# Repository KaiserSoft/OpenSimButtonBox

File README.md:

Modular Open Sim Racing Button Box
==================================

The Modular Open Button Box (MOBB) project is a complete open source solution to build your own button box. It provides complete plans on how to build your own 
Teensy 3.2 shield, button box ideas, box designs for 3D printers, drill tempaltes for your face plates or just ideas for your own design.    
The design is modular so you may pick and choose from various parts to design YOUR button box the way YOU imagine it.    

Design idea with UV-LEDs to provide illumunation when it is dark

Side by side box design    

Two of the boxes used for current development    

Example of pit limiter switch on older development board   

The PCB
===========
The PCB is a shield for the Teensy 3.2 micro controller board. You may use the provided schematic to build your own on a perfboard, use the provided gerber files to have one manfucatured or contact me to send you one.    
Assembly requires minor soldering skills but assembly is quite easy if you follow the instruction videos.       

The current version supports
* through hole component design for easy soldering
* 32 buttons
* 1 latching toggle switch with LED inside - used to enable/disable the pit limiter
* 3 rotary encoders
* 3 Auxillary ports providing 0-5Volt @ 100mA each
* one handed operation to adjust AUX ports (always have one hand on the steering wheel)
* fully open source in design and code
* code written using the Arduino IDE for easy customizations
* (Optional) 12Volt Fan Board with optical isolation between 12Volt supply and host PC. Connects to one AUX port and controls up to two fans.

INSTRUCTIONS & Sources List
===========================
Any documentation in the "Documentation" directory is not up to date anymore!    
I will produce a series of videos explaining how to build the PCB and how to configure the software.     
The build video is available here https://www.youtube.com/watch?v=iexbjr4jJTc      

This is an open source project - contributions are welcome!

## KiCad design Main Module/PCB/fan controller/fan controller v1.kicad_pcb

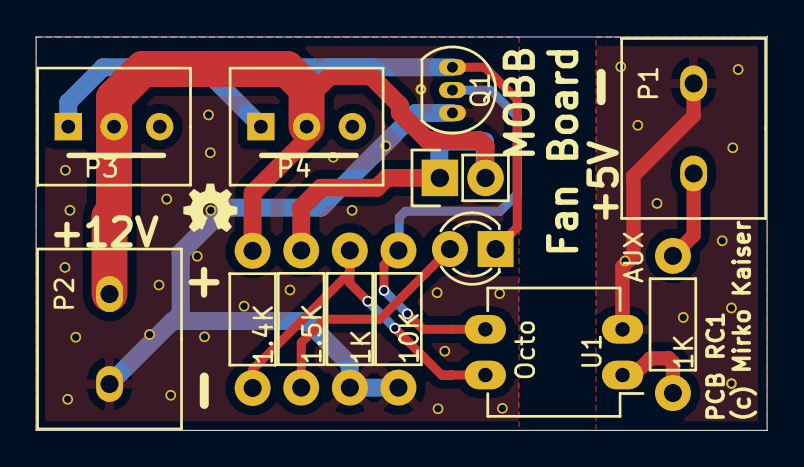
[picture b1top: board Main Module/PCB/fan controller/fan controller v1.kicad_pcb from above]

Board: 2 copper layers, 40.6 x 21.9 mm, 13 parts (0 on the bottom side), 9 nets.

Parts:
1.4K, 1.5K, 1K#2, 10K: R; Resistor_Horizontal_RM7mm
1K: 1K; Resistor_Horizontal_RM7mm
D1: LED; LED-3MM
P1: AUX; Screw_Terminal_5mm
P2: +12V Suppply; Screw_Terminal_5mm
P3, P4: Fan; Molex-KK-1x3P
P5: Jumper; Pin_Header_Straight_1x02
Q1: NPN; TO-92_Inline_Narrow_Oval
U1: Octo; DIP-4_W7.62mm_LongPads

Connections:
+5V: 1K.2, P1.2
+12V: 1.4K.1, 1.5K.2, P2.1, P3.2, P4.2, P5.1, P5.2
GND: 1K#2.1, 10K.1, P2.2, Q1.3
GNDA: P1.1, U1.2
unnamed: 1.4K.2, 1K#2.2, U1.4
unnamed: 1K.1, U1.1
unnamed: 10K.2, Q1.2, U1.3
unnamed: D1.1, P3.1, P4.1, Q1.1
unnamed: 1.5K.1, D1.2

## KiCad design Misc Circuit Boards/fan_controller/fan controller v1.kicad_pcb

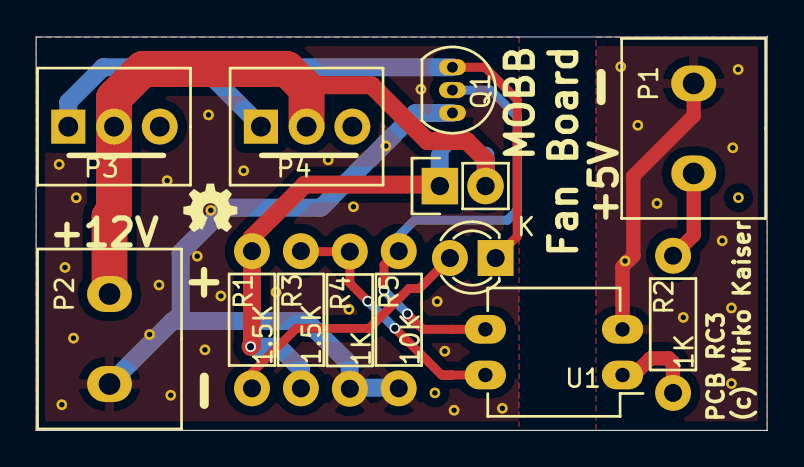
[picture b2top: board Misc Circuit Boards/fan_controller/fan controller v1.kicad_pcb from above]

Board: 2 copper layers, 40.6 x 21.9 mm, 13 parts (0 on the bottom side), 9 nets.

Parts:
D1: LED; LED-3MM
P1: AUX; Screw_Terminal_5mm
P2: +12V Suppply; Screw_Terminal_5mm
P3, P4: Fan; Molex-KK-1x3P
P5: Jumper; Pin_Header_Straight_1x02
Q1: NPN; TO-92_Inline_Narrow_Oval
R1, R3: 1.5K; Resistor_Horizontal_RM7mm
R2, R4: 1K; Resistor_Horizontal_RM7mm
R5: 10K; Resistor_Horizontal_RM7mm
U1: Ocot; DIP-4_W7.62mm_LongPads

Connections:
+5V: P1.2, R2.2
+12V: P2.1, P3.2, P4.2, P5.1, P5.2, R1.2, R3.1
GND: P2.2, Q1.3, R4.1, R5.1
GNDA: P1.1, U1.2
unnamed: D1.1, P3.1, P4.1, Q1.1
unnamed: D1.2, R1.1
unnamed: Q1.2, R5.2, U1.3
unnamed: R2.1, U1.1
unnamed: R3.2, R4.2, U1.4

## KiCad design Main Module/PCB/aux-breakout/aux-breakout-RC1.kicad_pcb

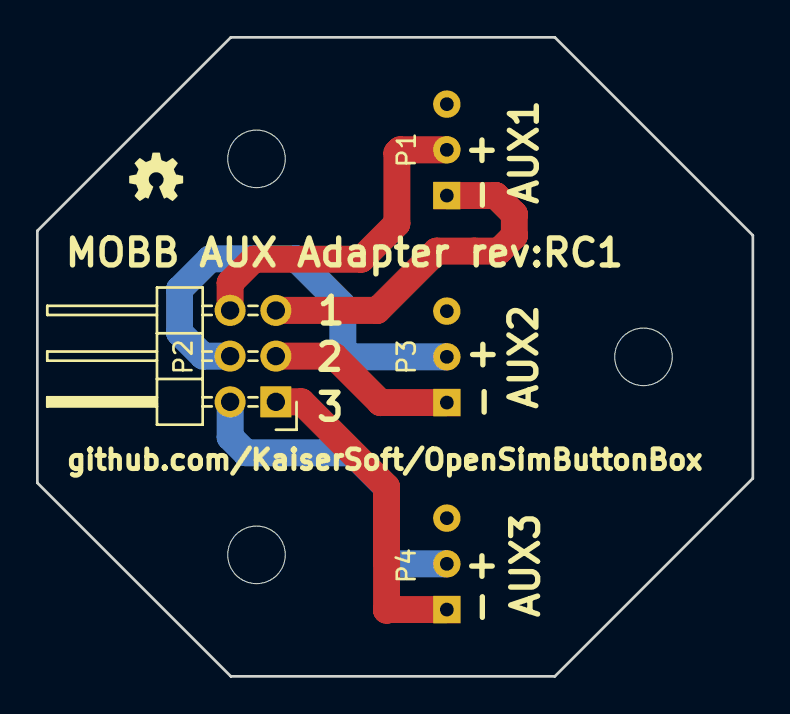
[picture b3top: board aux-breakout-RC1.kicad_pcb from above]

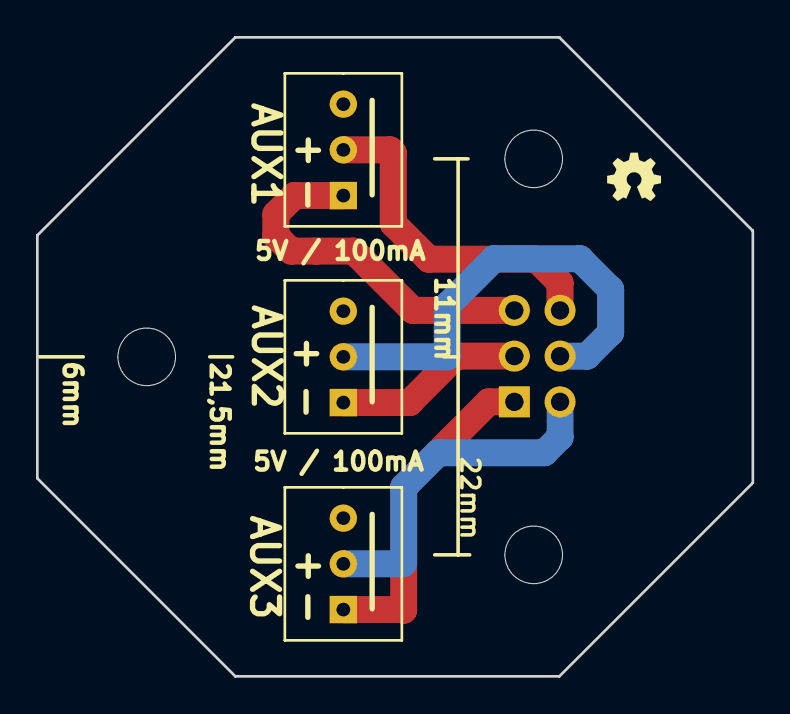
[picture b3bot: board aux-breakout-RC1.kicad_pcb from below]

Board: 2 copper layers, 39.8 x 35.5 mm, 4 parts (3 on the bottom side), 6 nets.

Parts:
P1: AUX1; Molex-KK-1x3P
P2: Aux1-3; Pin_Header_Angled_2x03
P3: AUX2; Molex-KK-1x3P
P4: AUX3; Molex-KK-1x3P

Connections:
/+5V: P2.4, P3.2
unnamed: P1.1, P2.5
unnamed: P1.2, P2.6
unnamed: P2.1, P4.1
unnamed: P2.2, P4.2
unnamed: P2.3, P3.1

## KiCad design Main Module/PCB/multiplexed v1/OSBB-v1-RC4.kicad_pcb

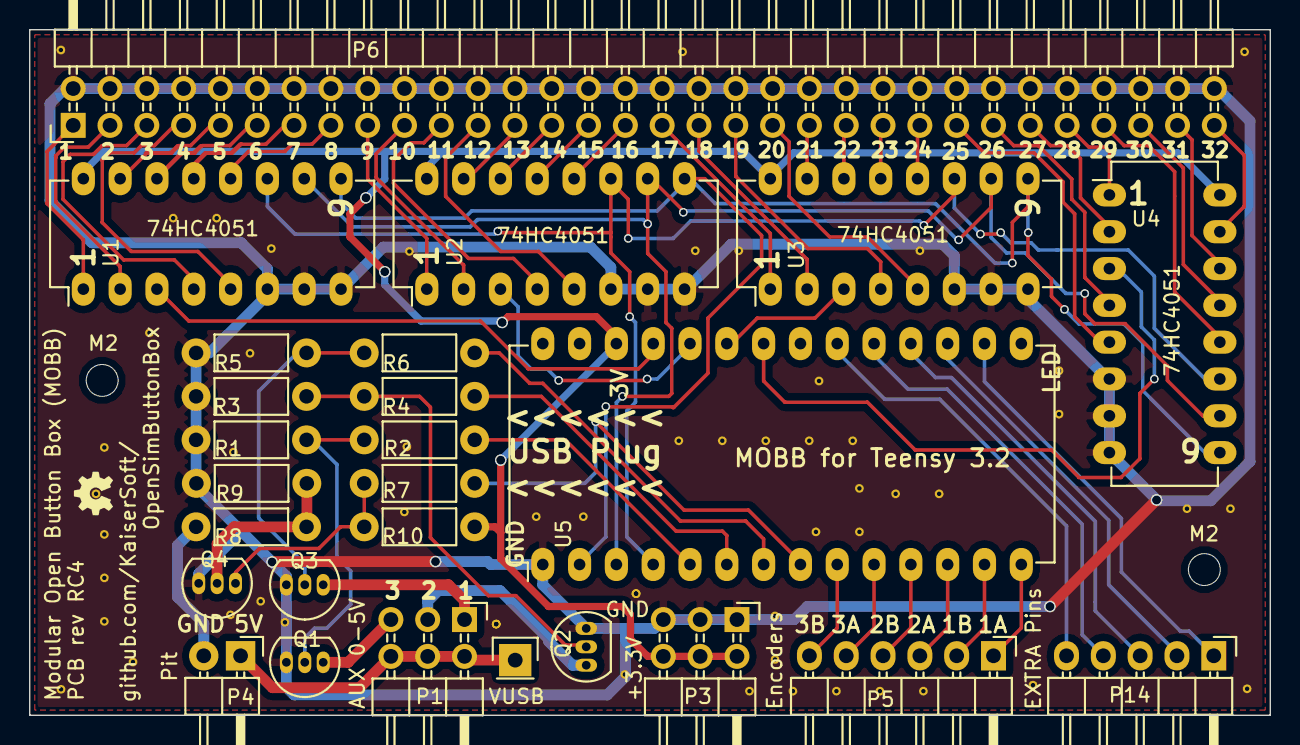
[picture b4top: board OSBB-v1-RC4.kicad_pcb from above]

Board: 2 copper layers, 85.6 x 47.3 mm, 26 parts (0 on the bottom side), 66 nets.

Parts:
P1: AUX 0-5V; Pin_Header_Angled_2x03
P2: VUSB; Pin_Header_Straight_1x01
P3: +3.3V; Pin_Header_Angled_2x03
P4: Pit; Pin_Header_Angled_1x02
P5: Encoders; Pin_Header_Angled_1x06
P6: BTN 1-32; Pin_Header_Angled_2x32
P14: EXTRA Pins; Pin_Header_Angled_1x05
Q1, Q2, Q3, Q4: NPN; TO-92_Inline_Narrow_Oval
R1, R3, R5, R9: 10K; Resistor_Horizontal_RM7mm
R2, R4, R6, R7, R8: 1K; Resistor_Horizontal_RM7mm
R10: 100K; Resistor_Horizontal_RM7mm
U1, U2, U3, U4: 74HC4051; DIP-16_W7.62mm_LongPads
U5: Teensy3.2; DIP-28_W15.24mm_LongPads

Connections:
+3V3: P3.2, P3.4, P3.6, R10.1, U1.16, U2.16, U3.16, U4.16, U5.26
+5V: P1.2, P1.4, P1.6, P2.1, P4.1
GND: P3.1, P3.3, P3.5, P6.2, P6.4, P6.6, P6.8, P6.10, P6.12, P6.14, P6.16, P6.18, P6.20, P6.22, P6.24, P6.26, P6.28, P6.30, P6.32, P6.34, P6.36, P6.38, P6.40, P6.42, P6.44, P6.46, P6.48, P6.50, P6.52, P6.54, P6.56, P6.58, P6.60, P6.62, P6.64, Q1.3, Q2.3, Q3.3, Q4.3, R1.2, R3.2, R5.2, R9.1, U1.6, U1.7, U1.8, U2.6, U2.7, U2.8, U3.6, U3.7, U3.8, U4.6, U4.7, U4.8, U5.1
unnamed: P1.1, Q3.1
unnamed: P1.3, Q2.1
unnamed: P1.5, Q1.1
unnamed: P4.2, R8.2
unnamed: P5.1, U5.14
unnamed: P5.2, U5.13
unnamed: P5.3, U5.12
unnamed: P5.4, U5.11
unnamed: P5.5, U5.10
unnamed: P5.6, U5.9
unnamed: P6.1, U1.1
unnamed: P6.3, U1.2
unnamed: P6.5, U1.4
unnamed: P6.7, U1.5
unnamed: P6.9, U1.15
unnamed: P6.11, U1.14
unnamed: P6.13, U1.13
unnamed: P6.15, U1.12
unnamed: P6.17, U2.1
unnamed: P6.19, U2.2
unnamed: P6.21, U2.4
unnamed: P6.23, U2.5
unnamed: P6.25, U2.15
unnamed: P6.27, U2.14
unnamed: P6.29, U2.13
unnamed: P6.31, U2.12
unnamed: P6.33, U3.1
unnamed: P6.35, U3.2
unnamed: P6.37, U3.4
unnamed: P6.39, U3.5
unnamed: P6.41, U3.15
unnamed: P6.43, U3.14
unnamed: P6.45, U3.13
unnamed: P6.47, U3.12
unnamed: P6.49, U4.5
unnamed: P6.51, U4.4
unnamed: P6.53, U4.2
unnamed: P6.55, U4.1
unnamed: P6.57, U4.12
unnamed: P6.59, U4.13
unnamed: P6.61, U4.14
unnamed: P6.63, U4.15
unnamed: P14.1, U5.16
unnamed: P14.2, U5.17
unnamed: P14.3, U5.18
unnamed: P14.4, U5.19
unnamed: P14.5, U5.20
unnamed: Q1.2, R1.1, R2.2
unnamed: Q2.2, R3.1, R4.2
unnamed: Q3.2, R5.1, R6.2
unnamed: Q4.1, R7.2, R10.2
unnamed: Q4.2, R8.1, R9.2
unnamed: R2.1, U5.5
unnamed: R4.1, U5.6
unnamed: R6.1, U5.7
unnamed: R7.1, U5.8
unnamed: U1.3, U5.25
unnamed: U1.9, U2.9, U3.9, U4.9, U5.2
unnamed: U1.10, U2.10, U3.10, U4.10, U5.3
unnamed: U1.11, U2.11, U3.11, U4.11, U5.4
unnamed: U2.3, U5.24
unnamed: U3.3, U5.23
unnamed: U4.3, U5.22

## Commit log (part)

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2016-05-27 * file dump from local repo
2016-05-28 * tweak
2016-05-28 * .md format tweaks
2016-05-28 * .md tweaks
2016-05-28 * tweaks
2016-05-28 * STL files for v2 body and face plate * added v3 with additional center post on top and bottom row
2016-05-29 * tweaked delays
2016-05-30 * working on documentation and organizing the repo structure
2016-06-03 * testing UV lamp mount
2016-06-04 * new base part for a 10mm LED lamp
2016-06-04 * cover for new UV LED mount
2016-06-04 * complete holder assembly for 10mm LED holder. untestet, LED holes are currently 11 mm. needs two M3x20mm screws and nuts
2016-06-04 * front of base is now rounded off
2016-06-04 * updated to fit on v4 box
2016-06-04 * update
2016-06-04 * updated angles since they where to shallow. tested previous design with 5mm UV LED. 10mm parts should be here in a few days
2016-06-04 * cleanup
2016-06-05 * desing updates for fuel module
2016-06-05 * new idea for side box .... why add more rotary encoders when the existing three work fine. instead add more buttons which may open the black box menu, then use existing encoders to edjust values * 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
2016-06-05 * added mounting points for circuit boards
2016-06-05 * STL files for new models
2016-06-05 * removed old images
2016-06-05 * updated
2016-06-05 * latest prot v3 image
2016-06-05 * added Prototype v3 image
2016-06-08 * 14 not 15 dedicated button positions
2016-06-12 * new face plates * increased hole size for push button from 12.2mm to 13mm to compensate for lip
2016-06-12 * prototype 3 outside images
2016-06-12 * working on new docu
2016-06-12 * signal wires
2016-06-12 * main board
2016-06-13 * main board dev
2016-06-16 * few more words
2016-06-25 * progress! will post a schematic once it passes the "smoke test" ;)
2016-06-26 * more Main Board images. Appears to work when I check it with a multimeter. Will write code to detect buttons presses next
2016-06-26 * port usage of Main Board on Teensy
2016-09-25 * update for multiplexer
2016-09-26 * code cleanup * removed duplicate functions * all push and toggle switches are now checked by the same function in non-multi plexed mode * cleanup * config file instructions
2016-09-26 * WIP for v5 case, new idea is not mount two main boxes next to or below another
2016-09-26 * Body v5 is taler to give more room for main board blow * tweaked code to match dev setup * AUX support - fan and UV LED support next
2016-09-27 * documentation assembly script
2016-09-30 * final prototype v5
2016-10-01 * first face plates for version 5 ... same size as version 4
2016-10-01 * updated description * enabled AUX 1 and AUX 2 by default
2016-10-02 * new images * tweaked v5 face plate
2016-10-02 * added settings to start fans on AUX1-3 at a higher RPM when the device is turned on
2016-10-02 * kicad schematic for multi plexed main board. this is a WIP
2016-10-15 * reduced PWM frequency to allow voltage regulation through an optical isolator tested with a 12V "noctua" fan * AUX ports where not initialized when multiplexing was disabled * found an issue when A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
2016-10-16 * added modifier key support to AUX keys * added PWM frequency setting to AUX options * added config option to enable/disable pit limiter support * added code to use a permanent switch (ON/OFF) as a 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
2016-10-16 * release_key() enabled for serial output * removed bad logic when detecting non AUX button presses
2016-10-16 * added more information for Serial.print (dev only)
2016-10-16 * enabled AUX3 again ... there was not bug
2016-10-16 * serial feedback when PWM frequency is set (dev only)
2016-10-16 * adjusted some buttons to match iRacing.com defaults
2016-10-17 * tweaked config options * now possible to set AUX ports to a fixed value and not enable a button to control PWM output of the port * added a few more compiler conditions to omit some AUX check when 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
2016-10-17 * moved fan ramp up code to setup. it was in main loop but only ran once * tweaked Serial.print for initial AUX port setup (dev only)
2016-10-23 * new images
2016-10-25 * working on KiCAD schematic
2016-10-26 * created Teensy 3.2 library part (very basic)
2016-10-26 * Added pin numbers to Teensy library part to match DIL-28 housing
2016-10-28 * updated schematic to use 2x32 pin header to make it easier to connect PCB * PCB is connected, still needs to be checked
2016-10-30 * added perimiter to PCB layout
2016-10-31 * tweaked a few traces
2016-10-31 * GND traces thicker from 0.25mm to 0.5mm * +5V traces thicker from 0.25mm to 0.75mm
2016-10-31 * PCB redesign as RC2. better part placement for shorter traces * adjusted the order of some pins connecting to the header to make routing those traces easier * thicker supply and ground traces
2016-11-01 * added circuit for pit limiter switch onto the PCB * added open HW logo
2016-11-01 * updated readme with RC3 info
2016-11-01 * correct URL
2016-11-01 * lib file for RC4
2016-11-01 * RC4 Gerber files - untested so far
2016-11-02 * two tracks to close. had this corrected on Gerber files to manfacturer but did not push it. this is the fix.
2016-11-02 * increased spacing around a few more traces. passes for 0,23mm spacing now
2016-11-03 * added solder pads for another fan header to the PCB. there is room ... might as well
2016-11-06 * corrected molex connectors on Fan PCB * added optional LED to show "ON" state
2016-11-08 * minor trace tweak
2016-11-16 * first batch of PCBs for RC4
2016-11-17 * ready for testing
2016-11-20 * should be correct now
2016-11-20 * moved button settings to BUTTONS.h
2016-11-20 * PCB RC5-DEV adjusting button schematic to pull input low * now with M3 mounting hols * fixed missing silkscreen
2016-11-20 * unsaved changes
2016-11-21 * PCB RC5-dev labels
2016-11-21 * changed orientation of cap to give more room around screw * adjusted distance between lower pins (aux, 3v...) * more labels
2016-11-21 * fixed missing tracks from last release
2016-11-21 * flooded with GND * added vias
2016-11-21 + moved position of label box
2016-11-21 BLOCKED
2016-11-21 * added a few labels since I don't export all vlues for the gerber files * gerber files for RC5
2016-11-21 * added support for "button auto hold" on AUX ports * added dev option to disable EEPROM writes * added option to enable an LED on a pin when AUX settings are active
2016-11-22 * removed debug values for button and auxmod. should not be needed anymore since the feature is working well
2016-11-22 * data sheets for parts used
2016-11-22 * RC1 final for fan controller * ordered V-CUT version today since that fits into 5*5cm order size
2016-11-23 * aux breakout PCB. this board will be mounted to the case and provide access to AUX connectors through a hole in the case. mounting hole dimensions on back of PCB
2016-11-28 * gerber files where missing F+B solder mask layers
2016-12-08 * code adjusted for PCB RC5 circuit design. should not work with non-multiplexed at the moment
2016-12-08 * PCB RC5 has arrived. Looks like the floating pin bug has been fixed. Multiplexed buttons are now pulled LOW through a 10K resistor when idle and HIGH when a button is pushed. final test when I scre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
2016-12-09 * code updates for PCB RC5
2016-12-10 * updates for RC5 * set ENCODER_DO_NOT_USE_INTERRUPTS
2016-12-10 * final tweaks. system assembled. will be testing this desing now
2016-12-10 * updated schematic with PTC fuse
2016-12-10 * gerber files for RC1 of aux breakout board
2016-12-11 * current work of PCB RC6 - WIP * added PTC fuses for 3.3V and 5V to protect the PC in case of accidental short circuit * added 2x1 straight pin header which connects to pin13. this may late be used 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
2016-12-11 * PCB RC6 gerber files
2016-12-12 * RC6 cleanup
2016-12-13 * Update for PCB RC6
2016-12-15 * fixed values in schematic
2016-12-15 * fan boards arrived, some holes are too tight. Corrected in RC2 PCB revision
2016-12-15 * ignore
2016-12-20 * tweaked
2016-12-20 * reorganizing the repository structure
2017-01-15 * renamed Code directory to be compatible with arduino
2017-01-15 * updated schematic for version 1.0 from RC6 * adjusted silkscreen positions * replaced RR6 and RR5 footprint, removed pin 1 indicator * C4 now through hole * removed vias from 32pin supply line
2017-01-15 * gerber files for PCB version 1.0
2017-01-15 * RC2 breakout board with correct hole size for 3 pin molex connector
2017-01-15 * RC2 fan board with correct hole size for 3 pin molex connector
2017-01-15 * renamed
2017-01-16 * pin changes for PCB RC6 and PCB 1.0 (AUX and pit limiter pins)
2017-01-16 * UV LED light testing connected to AUX port
2017-01-18 * working on SMD layout
2017-01-18 * bit messy but the layout should work. still WIP
2017-01-20 * RC1 for SMD PCB, still WIP
2017-01-21 * added top mounting hole to SMD PCB
2017-01-21 * added bottom mounting hole and ground connections
2017-01-21 * added ground vias
2017-01-22 * moved all components to top side to allow for cheaper manufcaturing * rearanged multiplexers to make room for bottom resistors
2017-02-12 * PCB v1.0 images
2017-02-26 * final tweaks to MainBoard SMD RC1 release. this is for testing only at this point
2017-03-10 * known issues update for fan board and PCB v1.0
2017-03-10 * fan controller board RC3 - this should fix the LED jumper issue from RC2 * increased size of some solder pads * all GND now with thermal relieve * moved LED down by 0,5mm to make "CUT" area larger 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
2017-03-11 * updated fan boards history
2017-03-13 * Added BOM for main board rev 1.0
2017-06-12 * PCB build video URL and splash screen
2017-06-22 * added 3D model for a G27 to Momo / Sparko / OMP wheel adapter
2017-06-23 * thicker to allow for the G27 screw heads to sink into the plate * momo / sparko screws should go in from behind
2017-06-24 * added v2 - two part adapter with enough room for the screws
2017-07-24 * Magnetic Paddle Shifter - RC1
2017-07-30 * 2cm thick spacer plate for Sparko - Momo wheels, Tested on OSW * Paddle Shifter mount to be used with the spacer
2017-07-30 * added "Shiter Priority", a more frequent check for two buttons when used as shifters. Result is very fast responds and support for fast shifting, for example when quickly downshifting from a high g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
2017-07-30 * added 110x40mm shifter paddle * renamed all paddles to indicate dimensions
2017-07-30 * simpler paddle design, smaller with weight saving holes
2017-07-31 * removed lines left over from development
2017-08-01 * added holes for counter sunk screw heads, this makes it possible to use M3x10mm screws. Tested with the "Shifter Paddle v2 - 100x42mm". Works good
2017-08-01 * updated readme with new minimum screw length for mounting the paddles
2017-08-01 * proof of concept for Arduino Nano based button box
2017-08-02 * enabled INPUT_PULLUP * added protocol info to README.md * tweaks before tests with actual buttons/shifters
2017-08-04 * reduced communication to bare minimum to speed everything up a tiny bit
2017-08-08 * Updated planned pinout for Arduino Nano * added button settings to Windows App to match button support
2017-08-08 * updated - can't use D13 without removing LED ... 13 buttons should be enough
2017-08-10 * new code. should be more efficient
2017-08-11 * corrected analog pin usage
2017-08-11 * quick hack for joystick since each axis has two positions
2017-08-15 * Updated Arduino Nano code base and info
2017-08-23 * Arduino Pro Micro testing
2017-08-28 * added new box style magnetic paddle shifter design
2017-08-28 * STM32F103C8T6 testing code
2017-08-28 * enabled LFS * added RC1 files for magnetic paddle shifter * added STEP 2014 3D model files
2017-08-28 * updated readme for LFS
2017-09-29 * image of version 1 wheel button box
2017-09-29 * small image file for readme
2017-09-29 * added image to readme
2017-10-07 * images for wheel button box - supported buttons and joystick
2017-10-07 * crop
2017-10-07 * updated guide
2017-10-31 * adjusted joystick center values * changed default to arrow keys
2017-10-31 * added "other axis lockout" so joystick only moves on direction at a time (x or y) instead of diagonal (x and y) * fixed invalid setting "JoysticksGetValues" should be "DebugJoysticksGetValues"
2019-03-16 * added support for hall effect shifters * added support for joystick + keyboard when in joystick mode
2019-03-16 * optimized
2019-03-17 * cleanup for manual

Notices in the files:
Main Module/PCB/fan controller/fan controller v1.kicad_pcb:
(c) 2016 Mirko Kaiser
